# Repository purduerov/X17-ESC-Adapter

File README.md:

# X17-ESC-Adapter
This board powers the ESCs and routes signals to and from the ESCs

Whenever you make a new part, download the datasheet and save it here _**and**_ with the part in the parts library

Always pull other people's changes before beginning to work
`git pull`

Be sure to push your changes after  working on them. Run:
1. `git add .` to add any files in this directory or a subdirectory
or `git add -u` to add any modified files
2. (Optional) `git clean -nX` to see what ignored files can be removed
	`git clean -fX` removes ignored files (Eagle backups)
3. `git commit -m "helpful commit message"` with a description of the work that you did
4. `git push` to push your work to github

Other helpful commands
* `git status` says information about modified and staged files
* `git log` shows the recent commits of the repository
* `git log filename.extension` show the recent commits for just that file
* `git checkout first-couple-letter-of-commit-id` lets you go back to a previous version
* `git checkout master` brings you back to the latest commit
* `git tag` lists the tags
* `git tag -a orderX -m "the version of the board placed for the X'th order"` tag a specific commit
* `git push --tags` needed to push tags to remote
* `git show orderX` show the commit log for the given tag
* `git checkout orderX` go back and interact with the files at the tagged commit

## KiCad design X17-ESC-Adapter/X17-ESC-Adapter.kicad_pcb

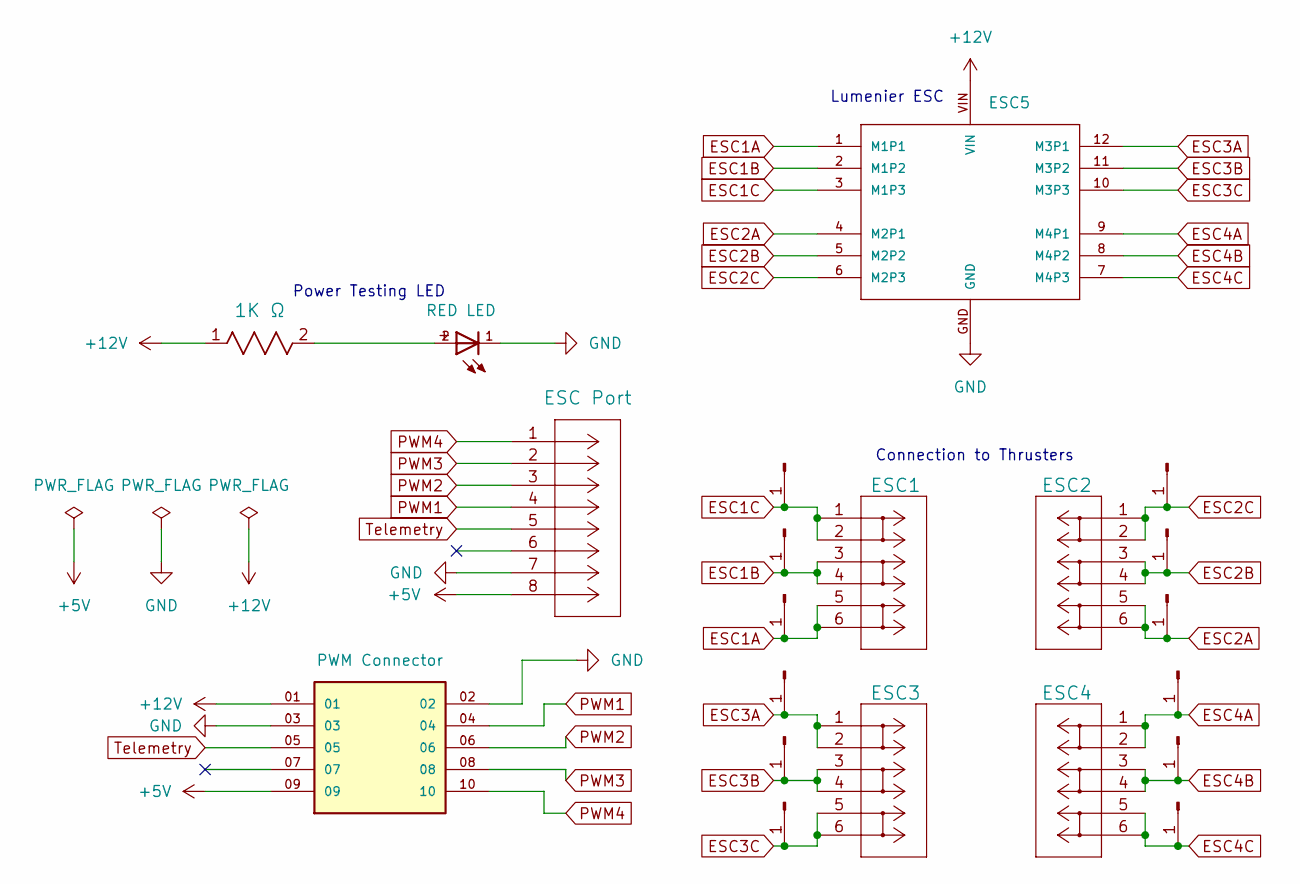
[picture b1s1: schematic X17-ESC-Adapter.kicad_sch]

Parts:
BM08B-SRSS-TBLFSN1: ESC Port; CONN_BM08B-SRSS-TBLFSN_JST
D1: RED LED; D_0805_2012Metric
ESC1, ESC2, ESC3, ESC4: 1824750000; CONN3_1824750000_WED
ESC5: LUMENIER
J1, J3, J4, J5, J6, J7, J8, J9, J10, J11, J12, J13: Pad for ESC; Pad for ESC Adapter
J2: PWM Connector; PWM, 12V, GND JST Connector; PARTREV R
R2: 1K Ω; R_0603_1608Metric

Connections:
+5V: BM08B-SRSS-TBLFSN1.8, J2.09
+12V: ESC5.VIN, J2.01, R2.1
ESC1A: ESC1.5, ESC1.6, ESC5.1 (M1P1), J4.1
ESC1B: ESC1.3, ESC1.4, ESC5.2 (M1P2), J3.1
ESC1C: ESC1.1, ESC1.2, ESC5.3 (M1P3), J1.1
ESC2A: ESC2.5, ESC2.6, ESC5.4 (M2P1), J7.1
ESC2B: ESC2.3, ESC2.4, ESC5.5 (M2P2), J6.1
ESC2C: ESC2.1, ESC2.2, ESC5.6 (M2P3), J5.1
ESC3A: ESC3.1, ESC3.2, ESC5.12 (M3P1), J8.1
ESC3B: ESC3.3, ESC3.4, ESC5.11 (M3P2), J10.1
ESC3C: ESC3.5, ESC3.6, ESC5.10 (M3P3), J9.1
ESC4A: ESC4.1, ESC4.2, ESC5.9 (M4P1), J11.1
ESC4B: ESC4.3, ESC4.4, ESC5.8 (M4P2), J12.1
ESC4C: ESC4.5, ESC4.6, ESC5.7 (M4P3), J13.1
GND: BM08B-SRSS-TBLFSN1.7, D1.1, ESC5.GND, J2.02, J2.03
unnamed: D1.2, R2.2
PWM1: BM08B-SRSS-TBLFSN1.4, J2.04
PWM2: BM08B-SRSS-TBLFSN1.3, J2.06
PWM3: BM08B-SRSS-TBLFSN1.2, J2.08
PWM4: BM08B-SRSS-TBLFSN1.1, J2.10
Telemetry: BM08B-SRSS-TBLFSN1.5, J2.05

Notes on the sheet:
Lumenier ESC
Power Testing LED
Connection to Thrusters

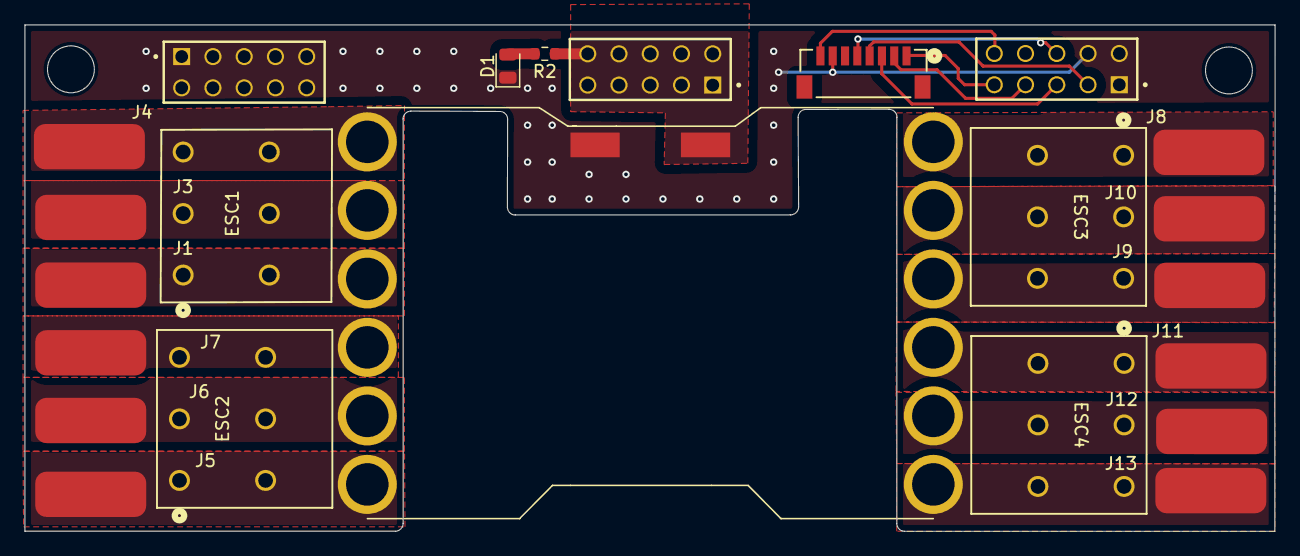
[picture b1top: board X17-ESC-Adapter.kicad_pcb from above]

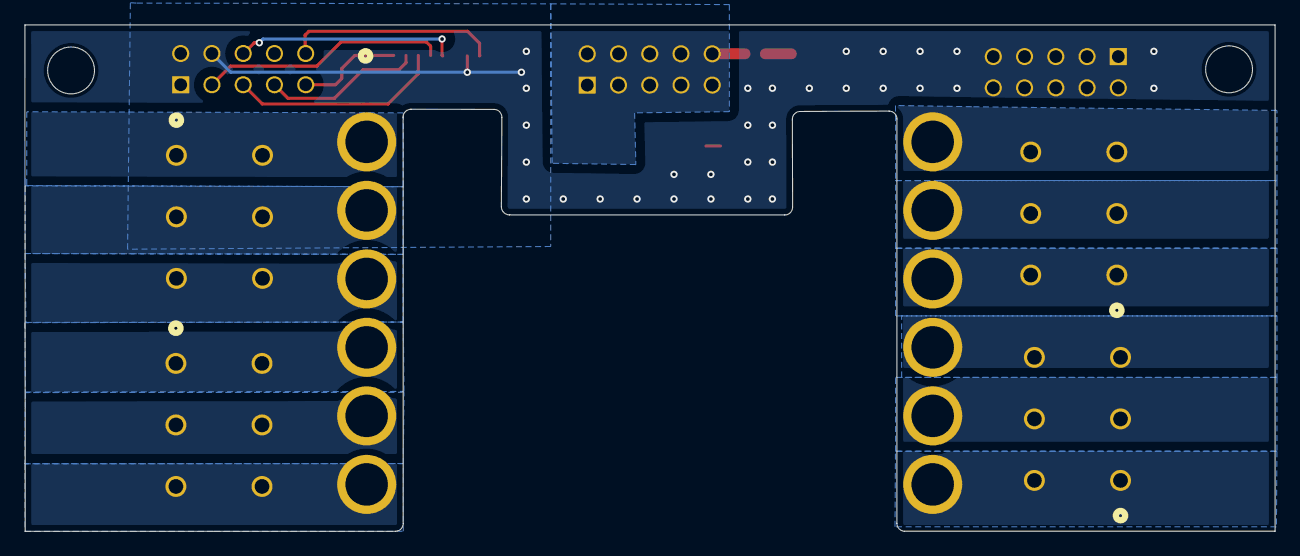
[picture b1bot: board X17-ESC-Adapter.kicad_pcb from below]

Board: 2 copper layers, 101.6 x 41.2 mm, 23 parts (2 on the bottom side), 21 nets.

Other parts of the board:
H1, H1#2: 6-32-HOLE

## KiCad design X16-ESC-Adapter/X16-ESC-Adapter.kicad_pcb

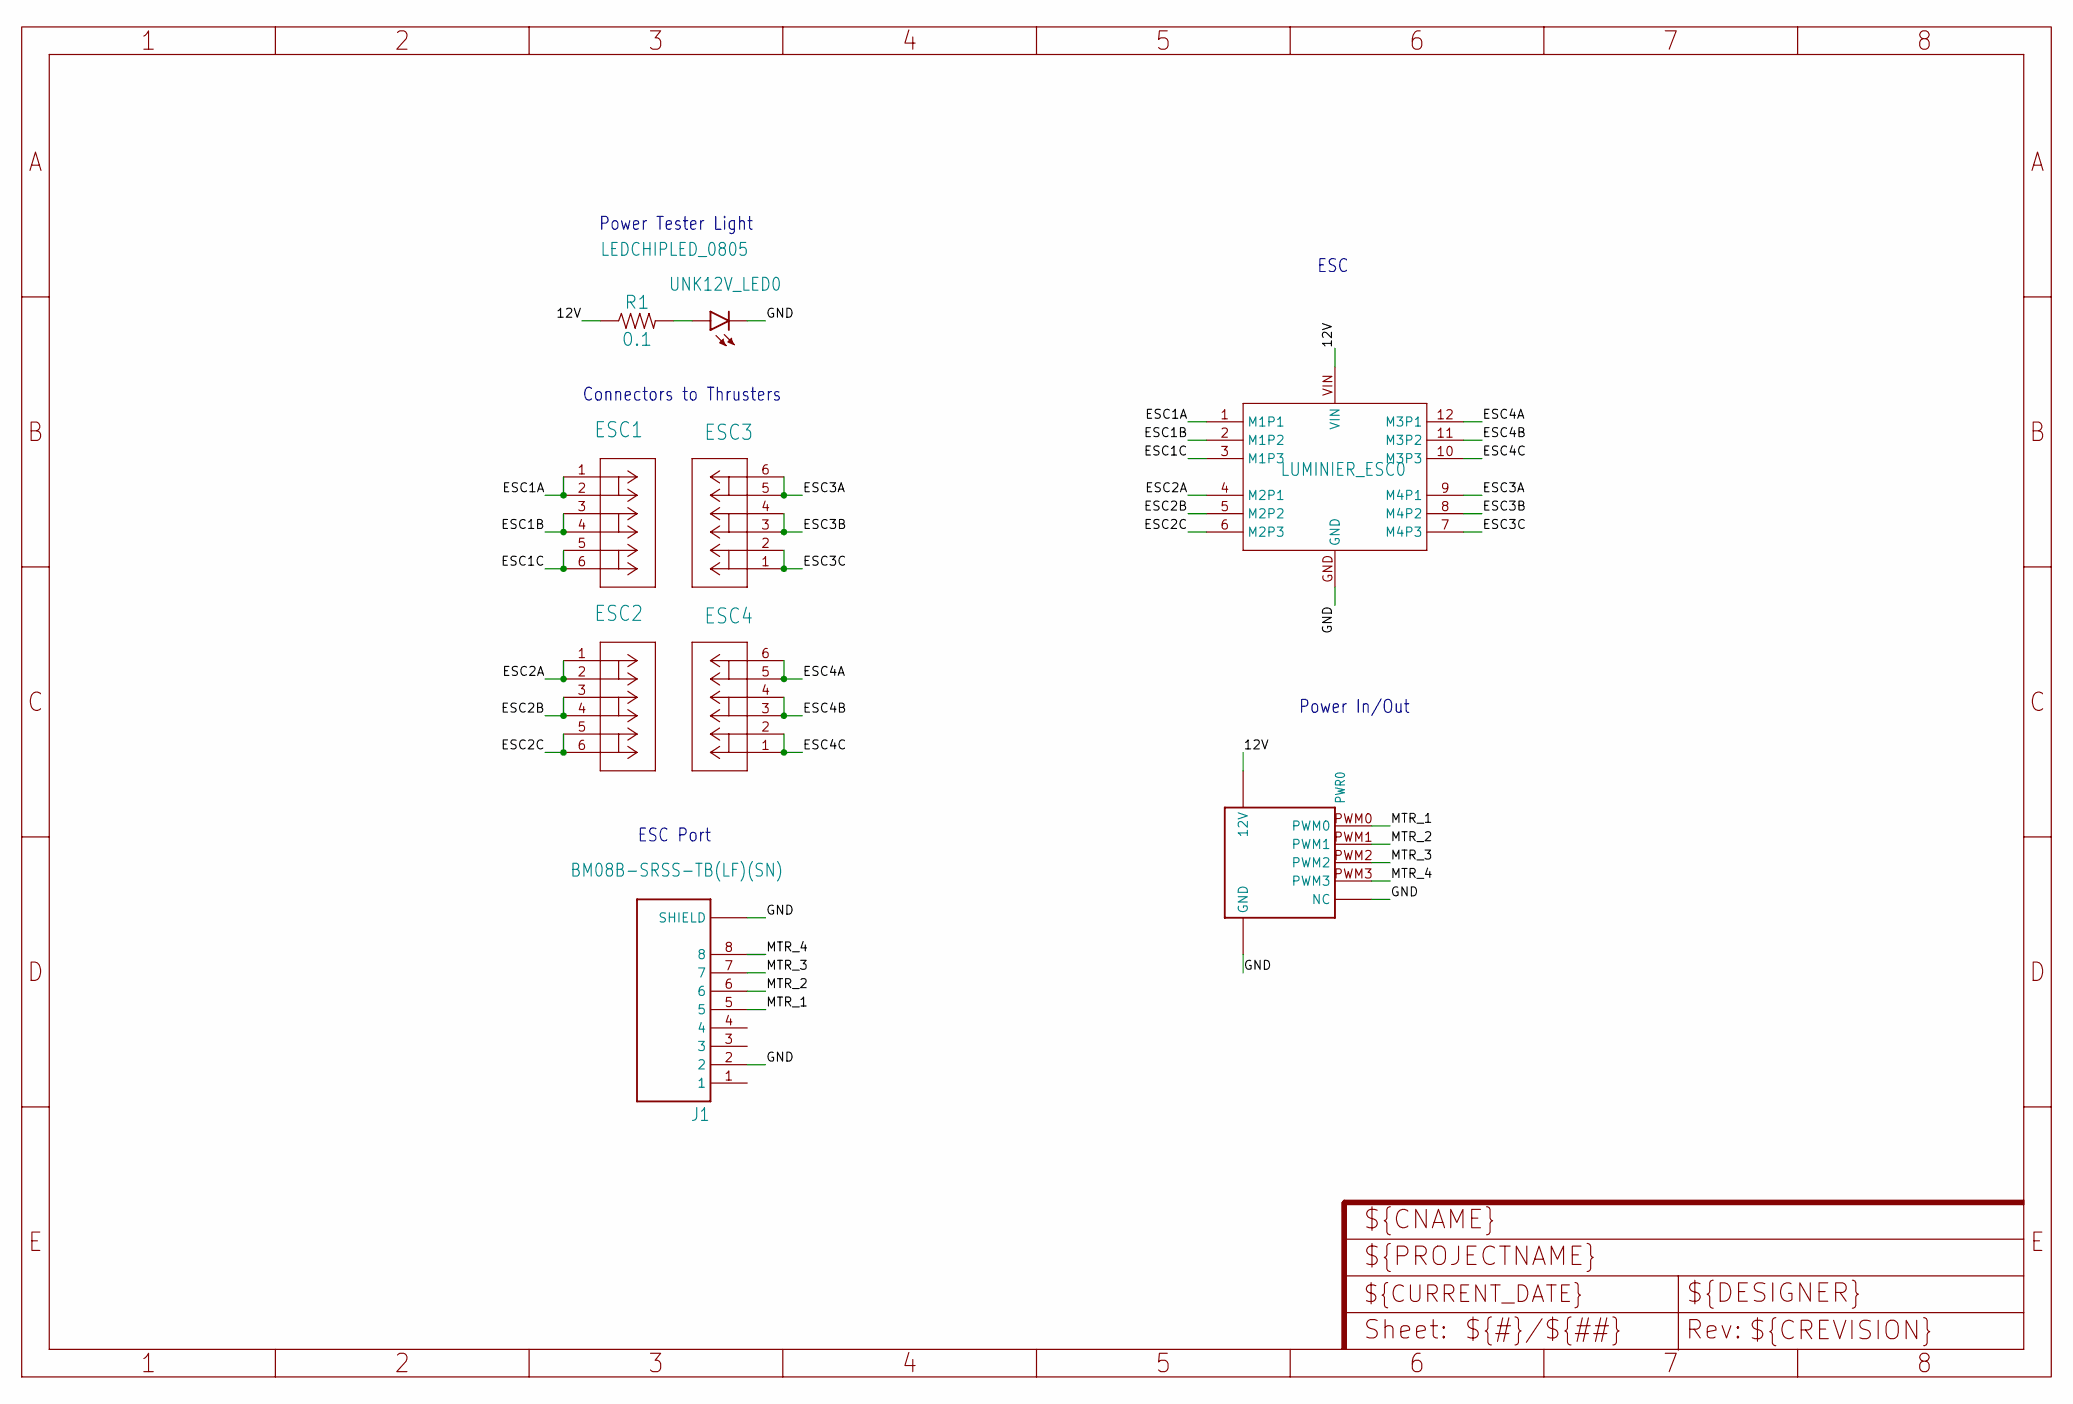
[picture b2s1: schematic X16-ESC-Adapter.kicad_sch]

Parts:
ESC1, ESC2, ESC3, ESC4: CONN_1824750000; CONN3_1824750000_WED
J1: BM08B-SRSS-TB(LF)(SN); JST_BM08B-SRSS-TB(LF)(SN)
LUMINIER_ESC0: LUMENIER
PWR0: CONN_BACKPLANE_ESC_ADAPTER
R1: 0.1; 0603
UNK12V_LED0: LEDCHIPLED_0805; CHIPLED_0805

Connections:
12V: LUMINIER_ESC0.VIN, PWR0.12V@3 (12V), PWR0.12V@4 (12V), PWR0.12V@5 (12V), PWR0.12V@6 (12V), PWR0.12V@7 (12V), PWR0.12V@8 (12V), PWR0.12V@9 (12V), PWR0.12V@10 (12V), PWR0.12V@11 (12V), PWR0.12V@12 (12V), R1.1
ESC1A: ESC1.1, ESC1.2, LUMINIER_ESC0.1 (M1P1)
ESC1B: ESC1.3, ESC1.4, LUMINIER_ESC0.2 (M1P2)
ESC1C: ESC1.5, ESC1.6, LUMINIER_ESC0.3 (M1P3)
ESC2A: ESC2.1, ESC2.2, LUMINIER_ESC0.4 (M2P1)
ESC2B: ESC2.3, ESC2.4, LUMINIER_ESC0.5 (M2P2)
ESC2C: ESC2.5, ESC2.6, LUMINIER_ESC0.6 (M2P3)
ESC3A: ESC3.5, ESC3.6, LUMINIER_ESC0.9 (M4P1)
ESC3B: ESC3.3, ESC3.4, LUMINIER_ESC0.8 (M4P2)
ESC3C: ESC3.1, ESC3.2, LUMINIER_ESC0.7 (M4P3)
ESC4A: ESC4.5, ESC4.6, LUMINIER_ESC0.12 (M3P1)
ESC4B: ESC4.3, ESC4.4, LUMINIER_ESC0.11 (M3P2)
ESC4C: ESC4.1, ESC4.2, LUMINIER_ESC0.10 (M3P3)
GND: J1.2, J1.S1 (SHIELD), J1.S2 (SHIELD), LUMINIER_ESC0.GND, PWR0.GND@1 (GND), PWR0.GND@2 (GND), PWR0.GND@3 (GND), PWR0.GND@4 (GND), PWR0.GND@5 (GND), PWR0.GND@6 (GND), PWR0.GND@7 (GND), PWR0.GND@8 (GND), PWR0.GND@9 (GND), PWR0.GND@10 (GND), PWR0.NC@1 (NC), PWR0.NC@2 (NC), PWR0.NC@3 (NC), PWR0.NC@4 (NC), PWR0.NC@5 (NC), PWR0.NC@6 (NC), UNK12V_LED0.C
MTR_1: J1.5, PWR0.PWM0
MTR_2: J1.6, PWR0.PWM1
MTR_3: J1.7, PWR0.PWM2
MTR_4: J1.8, PWR0.PWM3
unnamed: R1.2, UNK12V_LED0.A

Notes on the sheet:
Connectors to Thrusters
Power In/Out
ESC Port
ESC
Power Tester Light

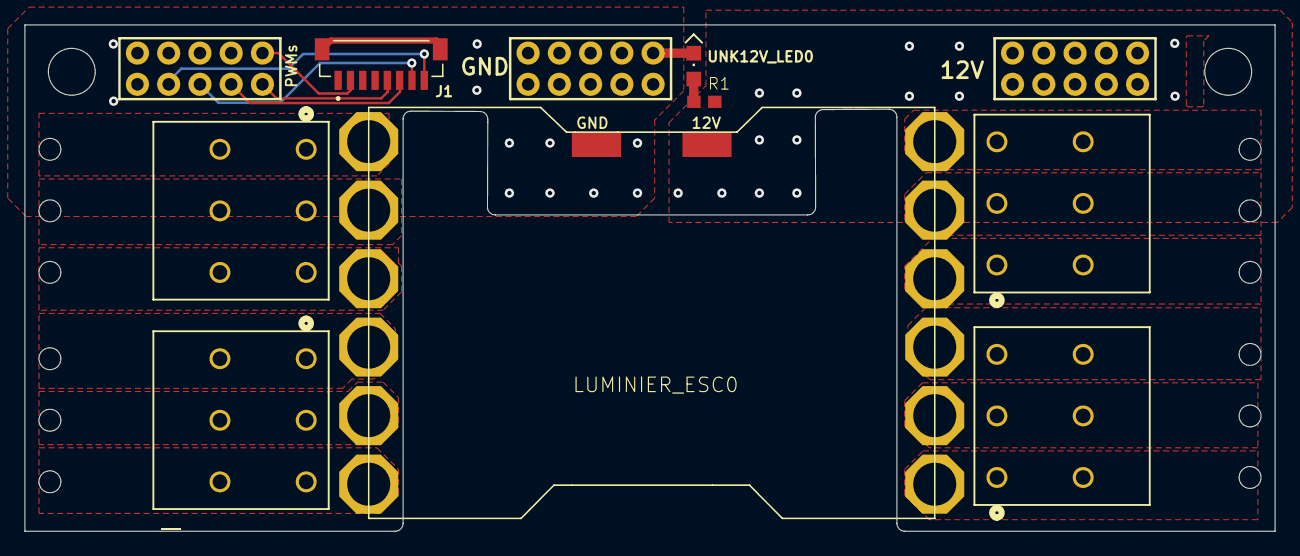
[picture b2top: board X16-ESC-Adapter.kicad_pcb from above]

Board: 2 copper layers, 101.6 x 41.1 mm, 23 parts (0 on the bottom side), 19 nets.

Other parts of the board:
@HOLE0, @HOLE1, @HOLE2, @HOLE3, @HOLE4, @HOLE5, @HOLE6, @HOLE7, @HOLE8, @HOLE9, @HOLE10, @HOLE11: (no value)
U$1, U$2: 6-32-HOLE

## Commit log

2024-09-25 test
2024-10-12 10/12/24
2024-10-12 board dimensions
2024-10-22 before design review
2024-10-24 made some changes
2024-10-26 final before alumni design review
2024-11-06 yeet
2024-11-09 daniel edit for correct pwm header position + polygon adjustment
2025-01-03 changes 1/3/25
2025-01-10 1/10/25 gerber files
2025-01-12 updated 3d model
